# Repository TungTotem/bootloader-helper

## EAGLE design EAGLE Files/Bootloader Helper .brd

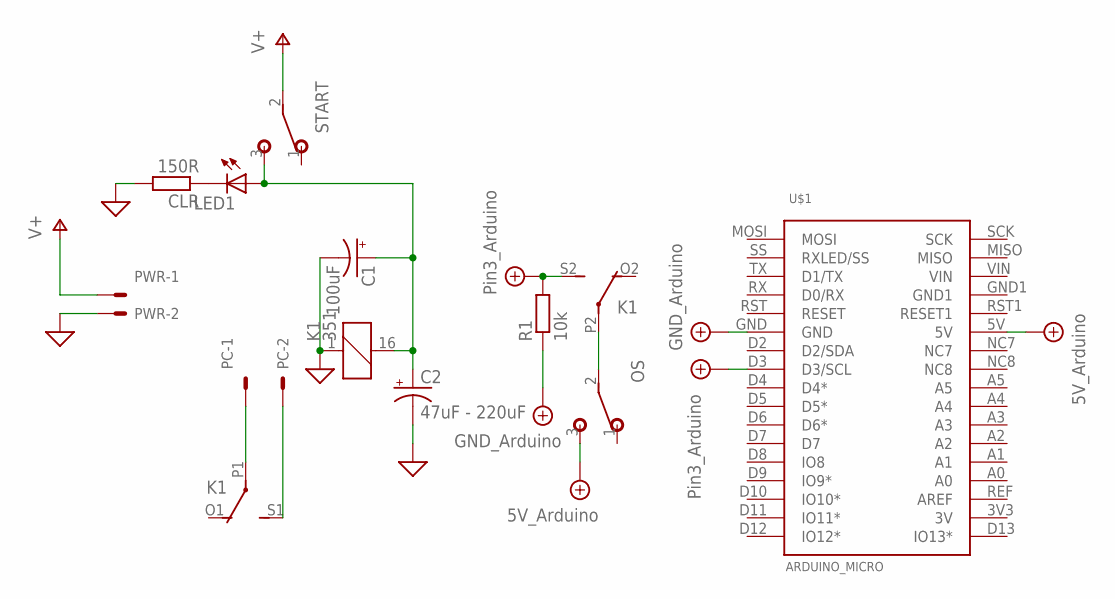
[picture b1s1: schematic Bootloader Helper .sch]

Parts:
C1: 100uF; E2-4
C2: 47uF - 220uF; E2,5-7
CLR: 150R; 0204/7
K1: 351
LED1: LED5MM
OS: SPDTPADS; SPDT
PC: ext. Power; 22-23-2021
PWR: ext. Power; 22-23-2021
R1: 10k; 0204/7
START: SPDTPADS; SPDT
U$1: ARDUINO_MICRO; ARDUINO-MICRO

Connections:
GND: C1.-, C2.-, CLR.2, K1.1, PWR.2
unnamed: K1.P1, PC.1
unnamed: C1.+, C2.+, K1.16 (2), LED1.A, START.3 (S)
unnamed: CLR.1, LED1.K (C)
unnamed: K1.S1 (S), PC.2
unnamed: K1.P2, OS.2
V+: PWR.1, START.2
VB: R1.1, U$1.GND
VC: K1.S2 (S), R1.2, U$1.D3 (D3/SCL)
VR: OS.3 (S), U$1.5V

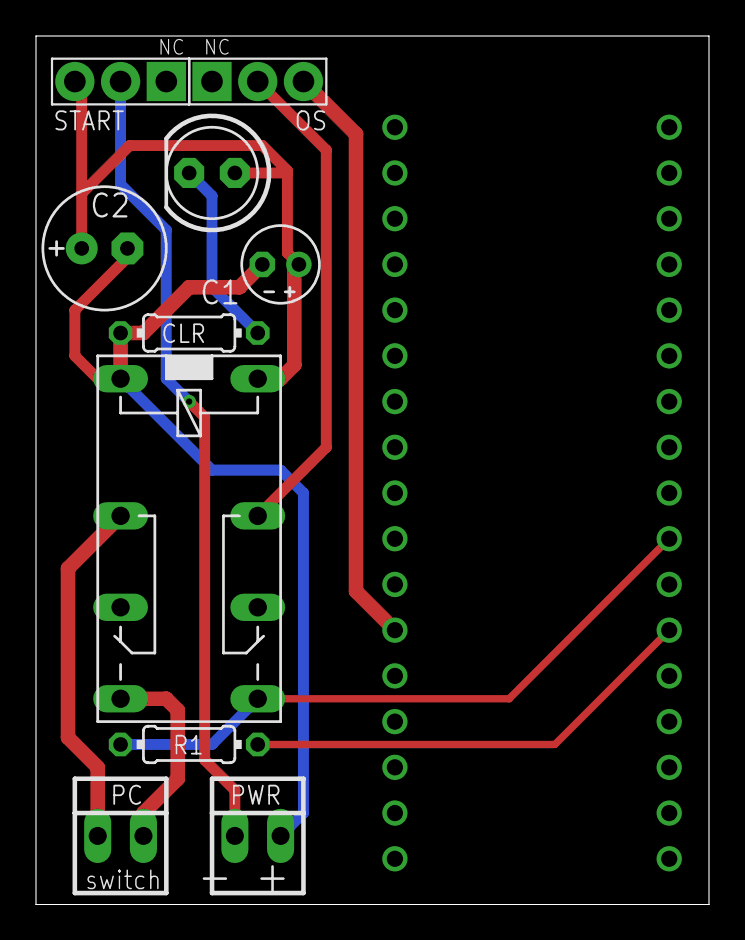
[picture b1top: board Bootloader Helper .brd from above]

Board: 2 copper layers, 37.4 x 48.2 mm, 11 parts (0 on the bottom side), 10 nets.
